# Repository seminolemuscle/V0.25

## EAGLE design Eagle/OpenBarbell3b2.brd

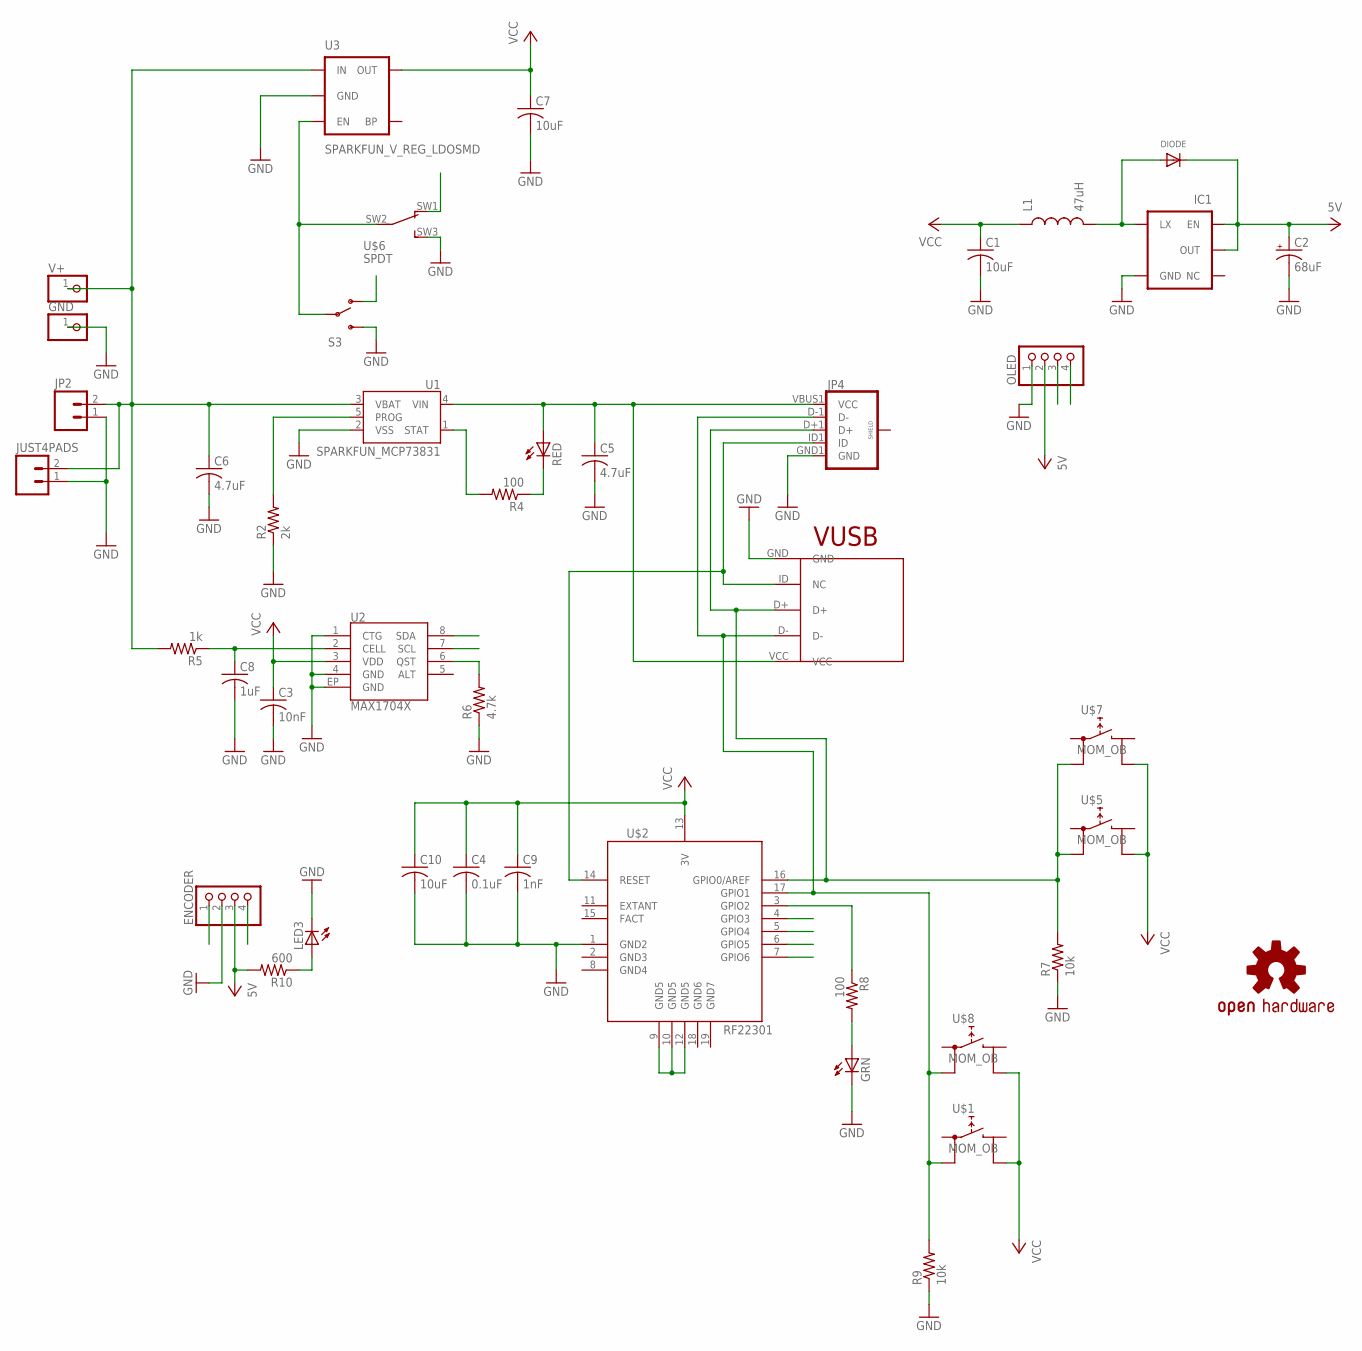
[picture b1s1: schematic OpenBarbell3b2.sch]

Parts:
C1, C7, C10: 10uF; C0805; MPN MC0805B102K101CT
C2: 68uF; SPARKFUN_EIA3528; MPN T520B686M006ATE025
C3: 10nF; C0805; MPN MC0805B103M500CT
C4: 0.1uF; C0805; MPN MC0805B104M160CT
C5, C6: 4.7uF; C0805; MPN MC0805B102K101CT
C8: 1uF; C0805; MPN C0805C105M4VACTU
C9: 1nF; C0805; MPN MC0805B102K101CT
DIODE: DIODESOD-123; SOD-123
ENCODER: PINHD-1X3CB; 1X03-CLEANBIG
GND: PINHD-1X1; 1X01
GRN: LEDCHIPLED_0805; CHIPLED_0805
IC1: SPARKFUN_V_REG_NCP1400SOT23-5; SPARKFUN_SOT23-5; MPN NCP1402SN33T1G
JP2: SPARKFUN_M02-JST-2MM-SMT; SPARKFUN_JST-2-SMD; MPN S2B-PH-SM4-TB(LF)(SN)
JP4: USB_MICROB_PLUGCONN-11752; USB-B-MICRO-SMD_V03
JUST4PADS: SPARKFUN_M02-JST-2MM-SMT; SPARKFUN_JST-2-SMD; MPN S2B-PH-SM4-TB(LF)(SN)
L1: 47uH; SPARKFUN_CR54; MPN SRF1280-470M
LED3: LED3MM; MPN MCL034SBLC
OLED: PINHD-1X3CB; 1X03-CLEANBIG
R2: 2k; R0805; MPN MCHP05W4F4701T5E
R4, R8: 100; R0805; MPN MCHP05W4F3300T5E
R5: 1k; R0805; MPN RR1220P-102-D
R6: 4.7k; R0805; MPN MCHP05W4F4701T5E
R7, R9: 10k; R0805; MPN MCHP05W4F1002T5E
R10: 600; R0805; MPN MMZ2012S601A
RED: LEDCHIPLED_0805; CHIPLED_0805
S3: SWITCH-SPDTSMD2; SWITCH-SPDT-SMD
U1: SPARKFUN_MCP73831; SPARKFUN_SOT23-5; MPN MCP73831T-2DCI/OT
U2: MAX1704X; TDFN-8
U3: SPARKFUN_V_REG_LDOSMD; SPARKFUN_SOT23-5; MPN MIC5205-3.3YM5 TR
U$1, U$5, U$7, U$8: MOM_OB; MOM_
U$2: RF22301; RFD22301
U$3: USB-MICRO-B-VERTICAL_SMD; USB-MICRO-B-VERTICAL-SMD
U$4: SPARKFUN_OSHW-LOGOL; SPARKFUN_OSHW-LOGO-L
U$6: SPDT
V+: PINHD-1X1; 1X01

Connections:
5V: C2.A (+), DIODE.C, ENCODER.3, IC1.1 (EN), IC1.2 (OUT), OLED.2, R10.2
12345: C6.1, JP2.2, JUST4PADS.2, R5.2, S3.1 (O), U1.3 (VBAT), U3.1 (IN), U$6.SW1, V+.1
DIR: ENCODER.4, U$2.4 (GPIO3)
GND: C1.2, C2.C (-), C3.2, C4.2, C5.2, C6.2, C7.2, C8.2, C9.2, C10.2, ENCODER.2, GND.1, GRN.C, IC1.4 (GND), JP2.1, JP4.GND1 (GND), JUST4PADS.1, LED3.K (C), OLED.1, R2.1, R6.1, R7.1, R9.1, S3.3 (S), U1.2 (VSS), U2.1 (CTG), U2.4 (GND), U2.EP (GND), U3.2 (GND), U$2.1 (GND2), U$3.GND, U$6.SW3
GND3: U$2.2 (GND3)
GND4: U$2.8 (GND4)
GND5: U$2.9 (GND5), U$2.10 (GND5), U$2.12 (GND5)
GND6: U$2.18 (GND6)
GND7: U$2.19 (GND7)
unnamed: R6.2, U2.6 (QST)
unnamed: DIODE.A, IC1.5 (LX), L1.P$2 (2)
unnamed: LED3.A, R10.1
unnamed: C8.1, R5.1, U2.2 (CELL)
unnamed: C5.1, JP4.VBUS1 (VCC), RED.A, U1.4 (VIN), U$3.VCC
unnamed: R4.1, RED.C
unnamed: R2.2, U1.5 (PROG)
unnamed: R4.2, U1.1 (STAT)
unnamed: GRN.A, R8.2
unnamed: R8.1, U$2.3 (GPIO2)
unnamed: S3.2, U3.3 (EN), U$6.SW2
unnamed: JP4.ID1 (ID), U$2.14 (RESET), U$3.ID (NC)
unnamed: JP4.D+1 (D+), R7.2, U$2.16 (GPIO0/AREF), U$3.D+, U$5.T2, U$7.T2
unnamed: JP4.D-1 (D-), R9.2, U$1.T2, U$2.17 (GPIO1), U$3.D-, U$8.T2
SCL: OLED.3, U2.7 (SCL), U$2.6 (GPIO5)
SDA: OLED.4, U2.8 (SDA), U$2.7 (GPIO6)
TACH: ENCODER.1, U$2.5 (GPIO4)
VCC: C1.1, C3.1, C4.1, C7.1, C9.1, C10.1, L1.P$1 (1), U2.3 (VDD), U3.5 (OUT), U$1.T4, U$2.13 (3V), U$5.T4, U$7.T4, U$8.T4

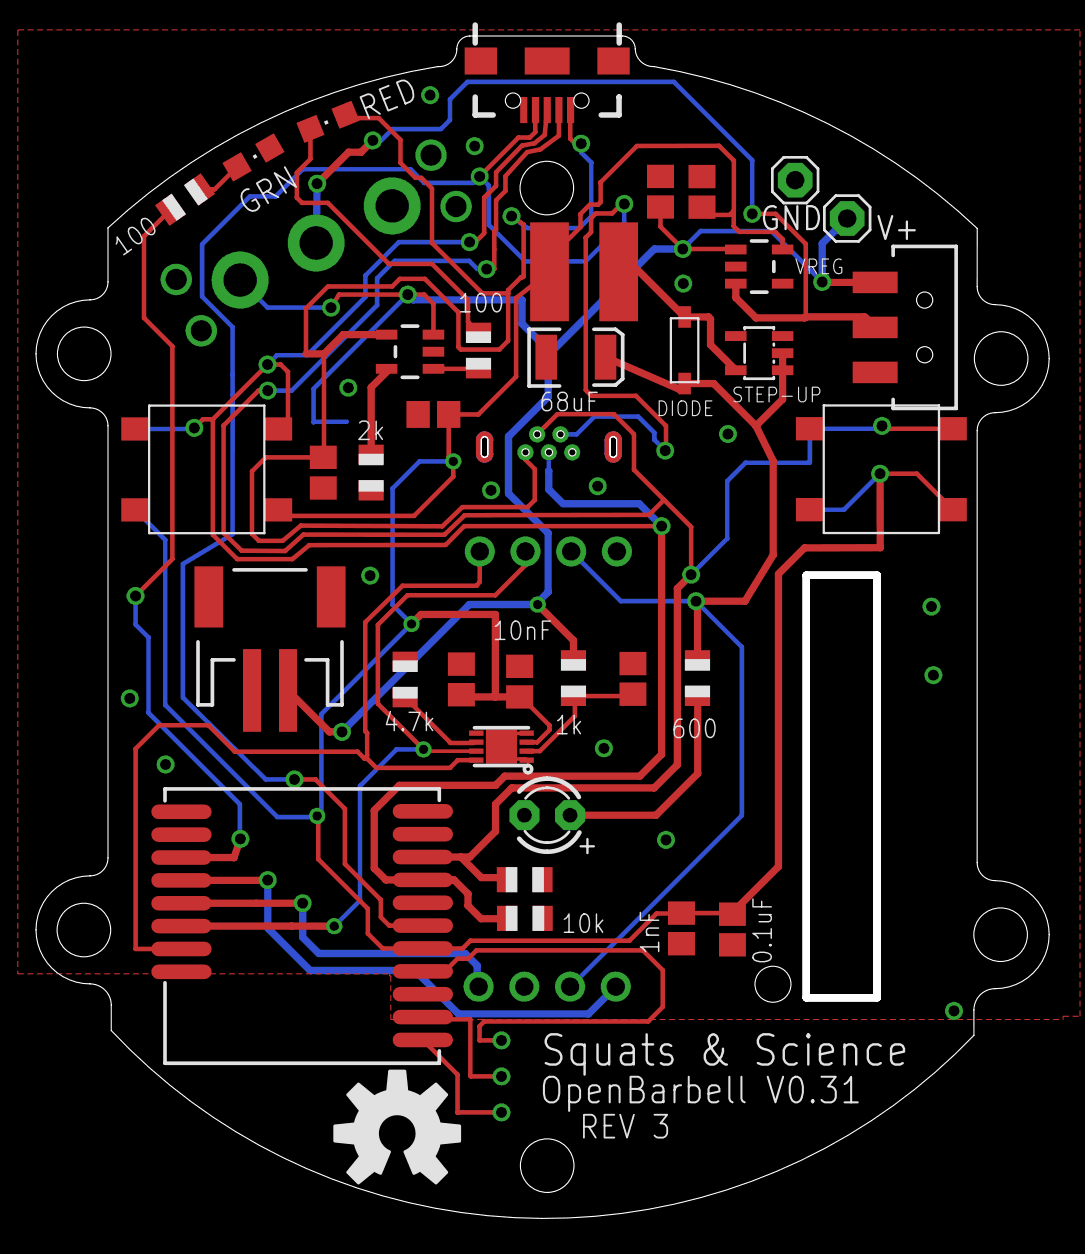
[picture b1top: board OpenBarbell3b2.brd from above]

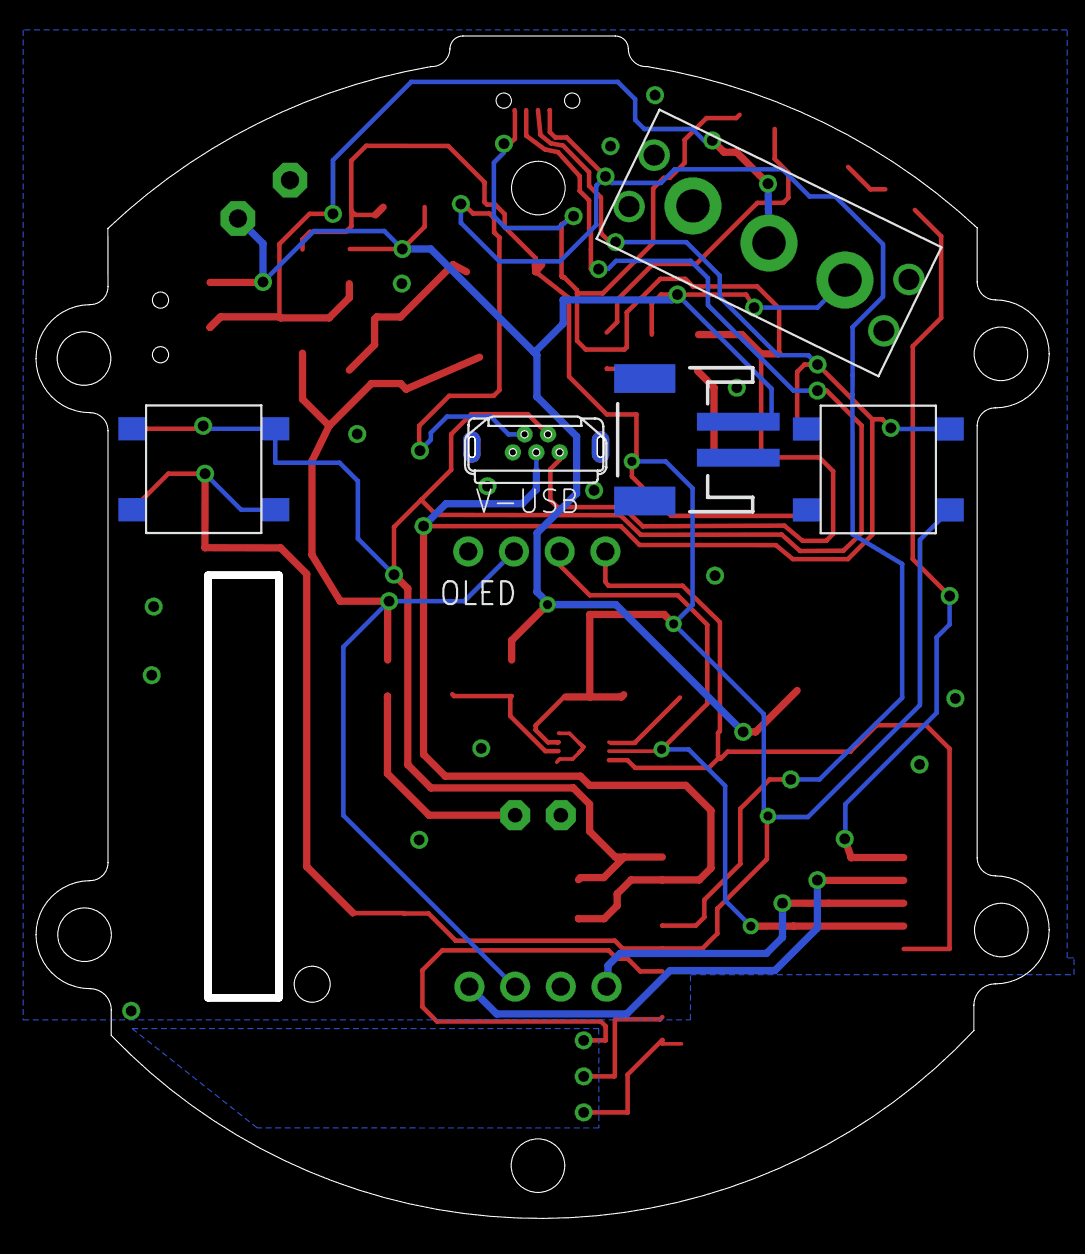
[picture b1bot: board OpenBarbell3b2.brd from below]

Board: 2 copper layers, 55.9 x 65.3 mm, 43 parts (6 on the bottom side), 23 nets.

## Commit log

2016-01-14 :space_invader: Added .gitattributes & .gitignore files
2016-01-14 Committing BOM, CAD, STL's, Eagle CAD, Arduino code, and reference designators for OpenBarbell V0.25
    Full suite of design files for making your own OpenBarbell device.
2016-05-04 adding string hook

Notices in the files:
parts and their libraries:
GeekAmmo: Licensing:Creative Commons ShareAlike 4.0 International - https://creativecommons.org/licenses/by-sa/4.0
